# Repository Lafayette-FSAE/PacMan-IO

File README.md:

# PacMan-IO
A breakout board for components which interface between the user and PacMan

Check out the assembly that this board belongs in [here](https://cad.onshape.com/documents/b7b97c21db578756ddc4e02a/w/427e6913ef587811d8900877/e/8a4ea13c14cc0e46974ebab7)

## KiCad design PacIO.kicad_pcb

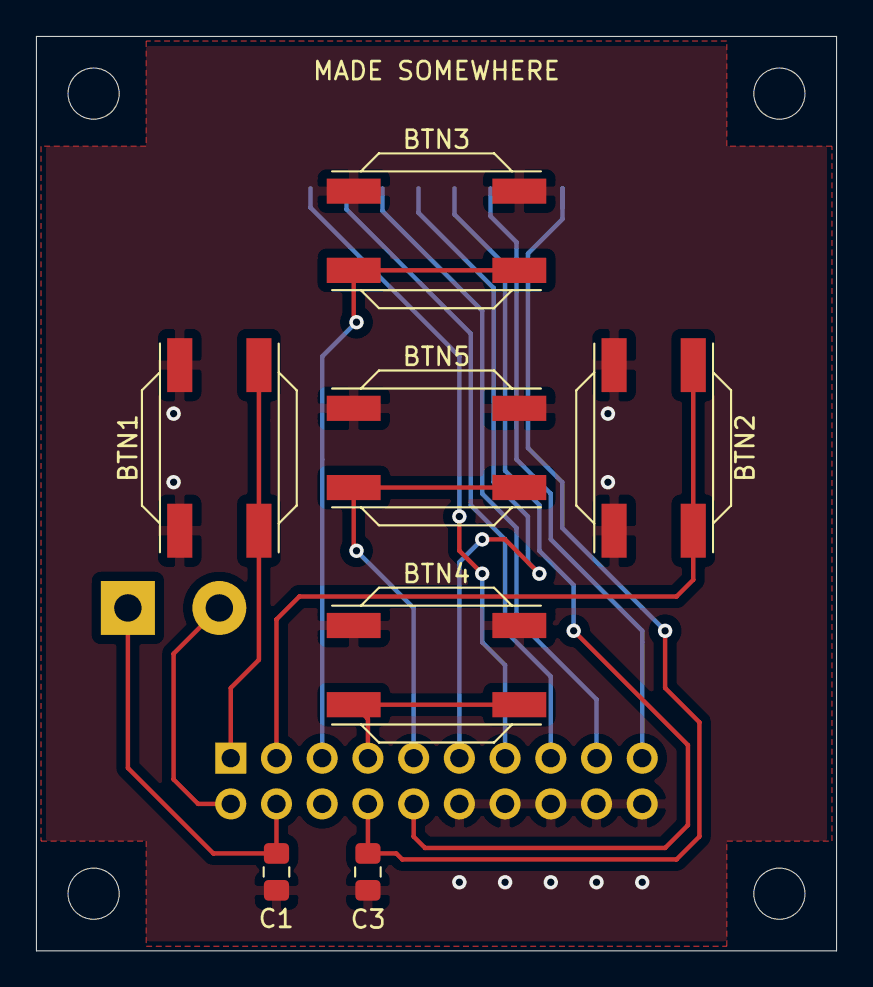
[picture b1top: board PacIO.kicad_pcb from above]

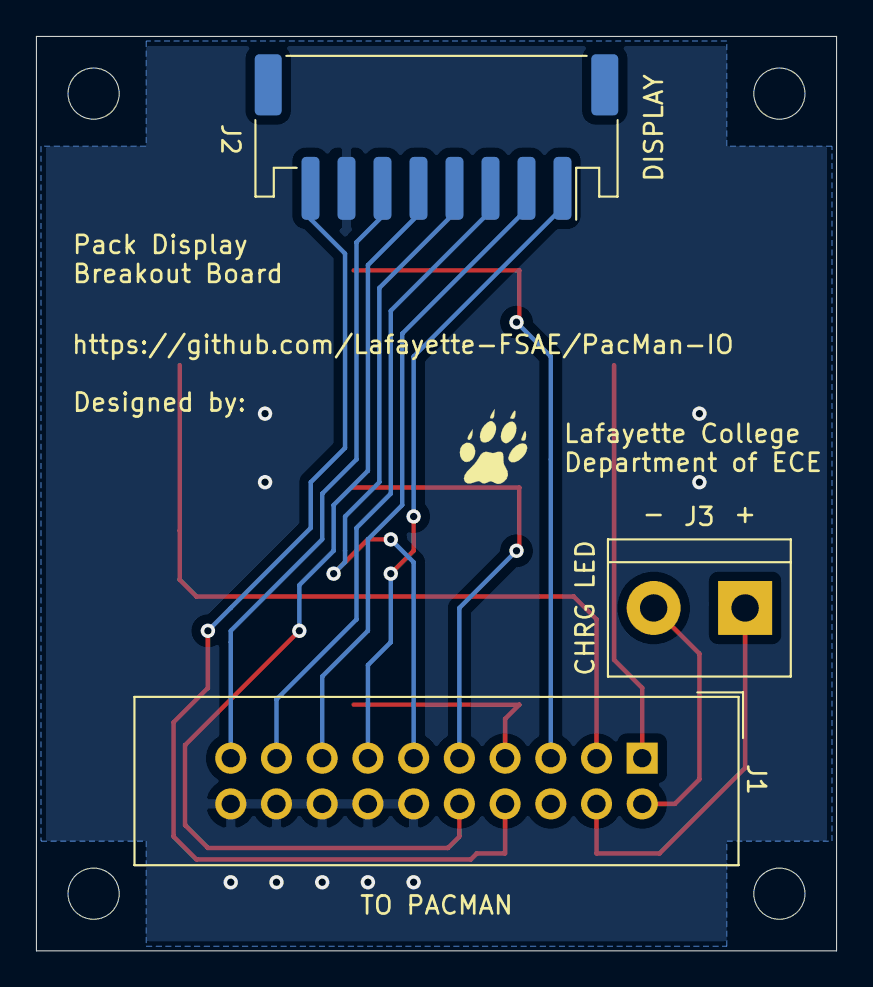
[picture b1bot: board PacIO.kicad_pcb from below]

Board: 2 copper layers, 44.4 x 50.8 mm, 15 parts (4 on the bottom side), 15 nets.

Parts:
BTN1: PushButton
BTN2: BTN_RIGHT; PushButton
BTN3: BTN_UP; PushButton
BTN4: BTN_DOWN; PushButton
BTN5: BTN_CENTER; PushButton
C1, C3: C; C_0805_2012Metric_Pad1.15x1.40mm_HandSolder
H1, H2, H3, H4: MountingHole_Pad; MountingHole_#4_NoPad
J1: PacMan_Connector; IDC-Header_2x10_P2.54mm_Vertical
J2: E-ink Display; JST_PH_S8B-PH-SM4-TB_1x08-1MP_P2.00mm_Horizontal
J3: Charge LED; TerminalBlock_bornier-2_P5.08mm
LOGO2: LeopardPawLogo; Paw

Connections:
+3V3: C3.1, J1.8, J2.8
+24V: C1.1, J1.4, J3.1
/BTN_CENTER: BTN5.2, J1.9
/BTN_DOWN: BTN4.2, J1.7
/BTN_LEFT: BTN1.2, J1.1
/BTN_RIGHT: BTN2.2, J1.3
/BTN_UP: BTN3.2, J1.5
/CHRGE_LED: J1.2, J3.2
/DISP_BUSY: J1.13, J2.1
/DISP_CLK: J1.10, J2.5
/DISP_CS: J1.11, J2.4
/DISP_DC: J1.17, J2.3
/DISP_DIN: J1.19, J2.6
/DISP_RST: J1.15, J2.2
GND: BTN1.1, BTN2.1, BTN3.1, BTN4.1, BTN5.1, C1.2, C3.2, J1.12, J1.14, J1.16, J1.18, J1.20, J2.7

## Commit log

2019-11-14 Oops, almost forgot to put this in a repository
2019-11-17 Redrew Schematic
2019-11-18 Logos
2019-11-18 Fixed Schematic to match PacMan
2019-11-19 layout
2020-01-22 pin changes
2020-01-23 Not sure, did this a while ago
2020-02-13 Moved Parts Positions for final panel
2020-02-13 Dimensions and Edge cuts
2020-02-13 Routing
2020-02-13 cosmetic fix
2020-02-13 Added Flair
2020-02-13 More Cosmetic things
2020-02-13 New Origin
2020-02-14 Buttons Line up
2020-03-03 Changed mounting pads to have no pad, changed some traces to reflect the button footprint change, moved the ground planes back from the screwholes
2020-03-03 Fixed button spacing and positioning, some silkscreen stuff, some footprints
